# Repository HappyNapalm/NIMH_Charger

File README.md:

# NIMH_Charger
A Nickel Metal Hydride battery charger

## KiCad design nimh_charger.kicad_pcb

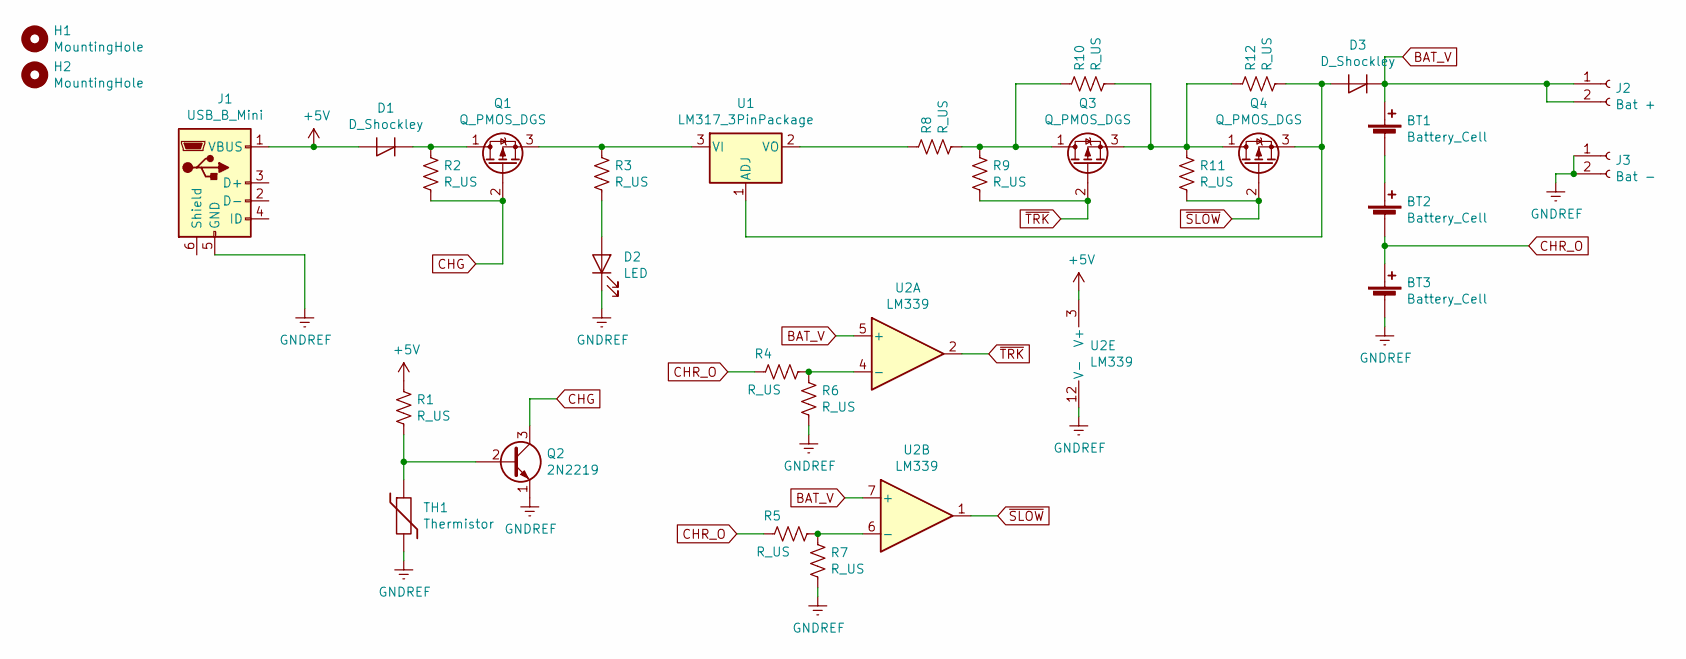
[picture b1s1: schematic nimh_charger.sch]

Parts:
BT1, BT2, BT3: Battery_Cell; BatteryHolder_Keystone_2466_1xAAA
D1, D3: D_Shockley; D_0805_2012Metric
D2: LED; D_0805_2012Metric
H1, H2: MountingHole; MountingHole_3mm
J1: USB_B_Mini; USB_Mini-B_Lumberg_2486_01_Horizontal
J2: Bat +; TerminalBlock_RND_205-00001_1x02_P5.00mm_Horizontal
J3: Bat -; TerminalBlock_RND_205-00001_1x02_P5.00mm_Horizontal
Q1, Q3, Q4: Q_PMOS_DGS; SOT-23
Q2: 2N2219; SOT-23
R1, R2, R3, R4, R5, R6, R7, R8, R9, R10, R11, R12: R_US; R_0805_2012Metric
TH1: Thermistor; TerminalBlock_RND_205-00001_1x02_P5.00mm_Horizontal
U1: LM317_3PinPackage; SOT-223-3_TabPin2
U2: LM339; SOIC-14_3.9x8.7mm_P1.27mm

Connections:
+5V: D1.2 (A), J1.1 (VBUS), R1.1, U2.3 (V+)
BAT_V: BT1.1 (+), D3.1 (K), J2.1, J2.2, U2.5 (+), U2.7 (+)
CHG: Q1.2 (G), Q2.3 (C), R2.1
CHR_O: BT2.2 (-), BT3.1 (+), R4.2, R5.2
GNDREF: BT3.2 (-), D2.1 (K), J1.5 (GND), J3.1, J3.2, Q2.1 (E), R6.1, R7.1, TH1.2, U2.12 (V-)
unnamed: BT1.2 (-), BT2.1 (+)
unnamed: D1.1 (K), Q1.1 (D), R2.2
unnamed: D2.2 (A), R3.1
unnamed: D3.2 (A), Q4.3 (S), R12.1, U1.1 (ADJ)
unnamed: Q1.3 (S), R3.2, U1.3 (VI)
unnamed: Q2.2 (B), R1.2, TH1.1
unnamed: Q3.1 (D), R8.1, R9.2, R10.2
unnamed: Q3.3 (S), Q4.1 (D), R10.1, R11.2, R12.2
unnamed: R4.1, R6.2, U2.4 (-)
unnamed: R5.1, R7.2, U2.6 (-)
unnamed: R8.2, U1.2 (VO)
~SLOW~: Q4.2 (G), R11.1, U2.1
~TRK~: Q3.2 (G), R9.1, U2.2

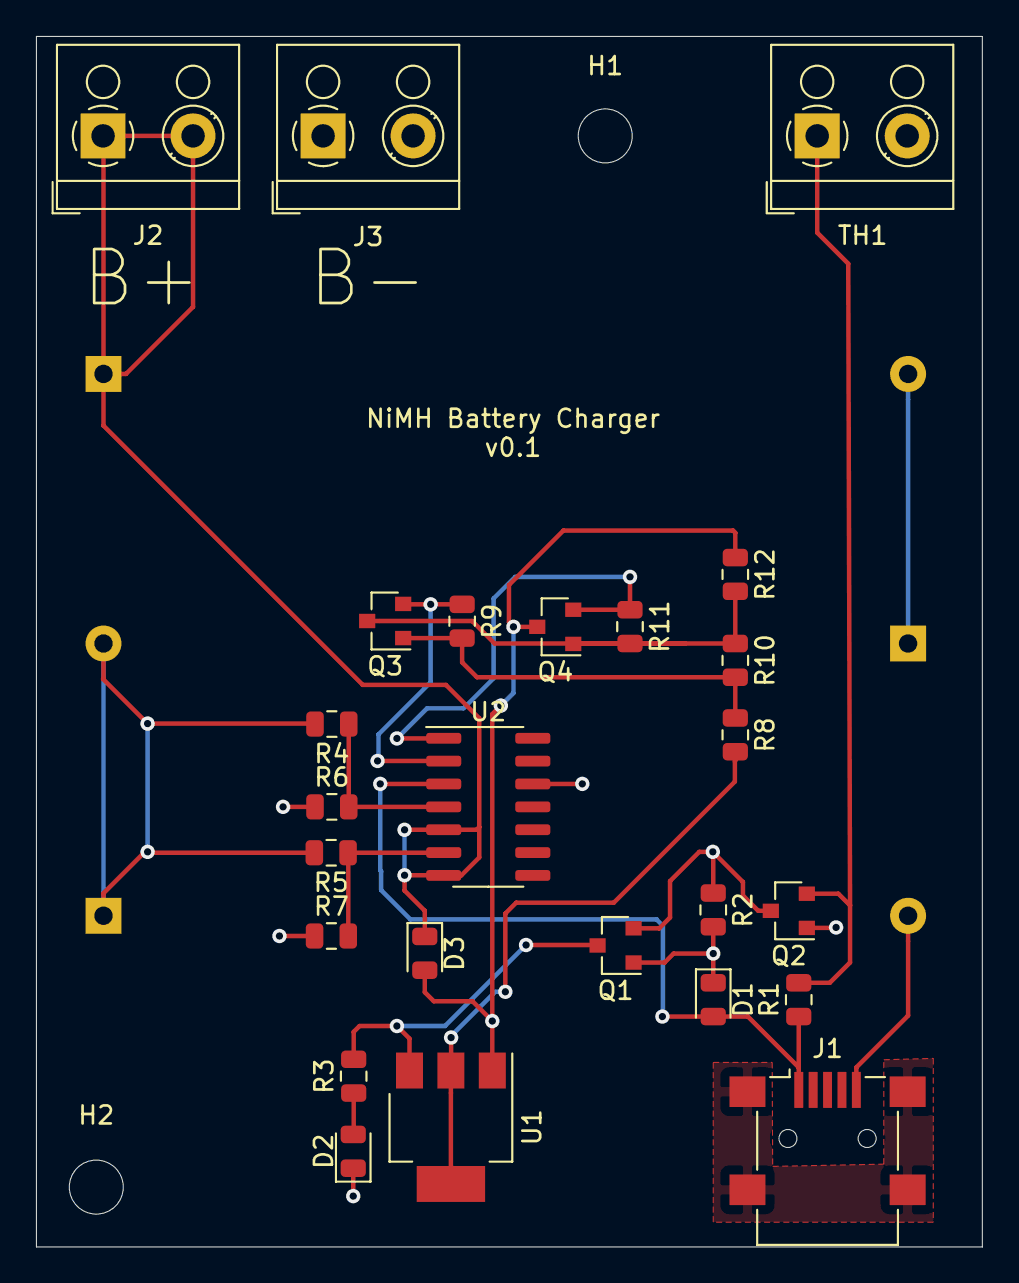
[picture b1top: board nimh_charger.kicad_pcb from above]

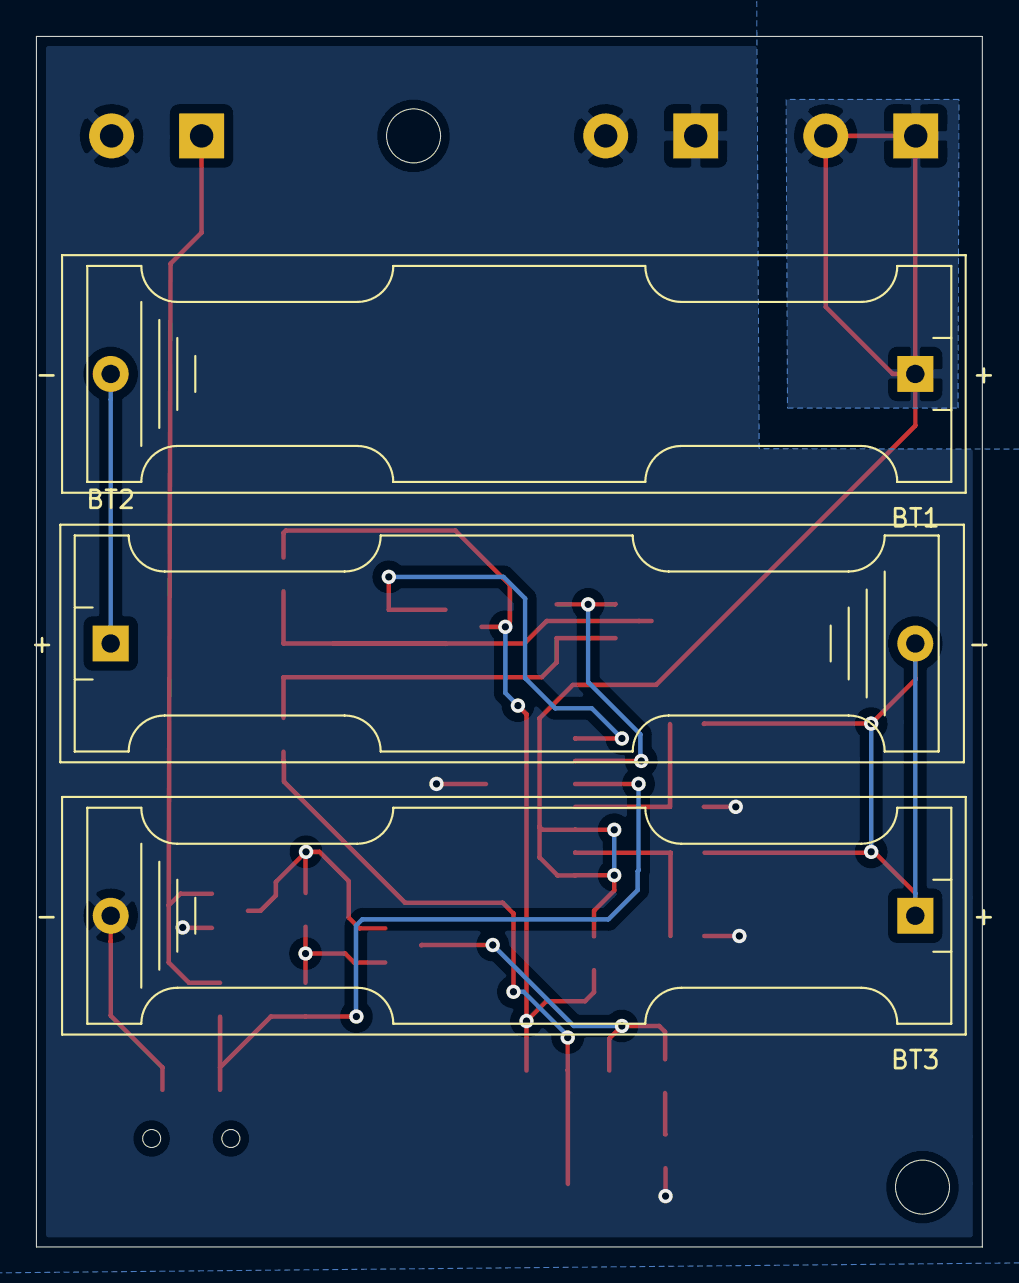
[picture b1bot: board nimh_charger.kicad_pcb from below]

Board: 2 copper layers, 52.6 x 67.2 mm, 30 parts (3 on the bottom side), 18 nets.

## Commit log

2021-03-14 Saving inital schematic.
2021-05-23 Placed parts on board file. Need to verify the bom before doing more layout
2021-06-02 Sorted out some footprints. Working on layout and placement.
2021-06-03 review the design
2021-08-07 Added some mounting holes
